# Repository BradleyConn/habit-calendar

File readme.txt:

This project contains everything used to construct a Habit Calender inspired from Simone Geirtz https://yetch.store/products/every-day-goal-calendar

This project contains the PCB designs designed in kicad as well as BOM and position files that wer sent off to JLCPCB for manufacturing.

Each board cost around $4 to make and ship and contains two PY32F002A microcontrollers and 32 lights/buttons. It takes 16 boards to make a full 365 day calendar.

The lights are ws2812b which provide endless lighting possibilities to be used outside of a calender concept. The LEDs can be controlled from the microcontroller with a bitbanged driver. A neat accomplishment from a super cheap 8 MHz microcontroller.

This wasn't intended to be public facing yet so the code is somewhat messy from when I was just trying to protoype stuff out, and documentation is not the best. In the software folder, the standalone folder is what you want, but check the readme for helpful info. Hopefully I can find some time to clean everything up.

More information and pictures can be found on www.bradleyconn.space
I need to properly cross link everything still. Sorry about that.

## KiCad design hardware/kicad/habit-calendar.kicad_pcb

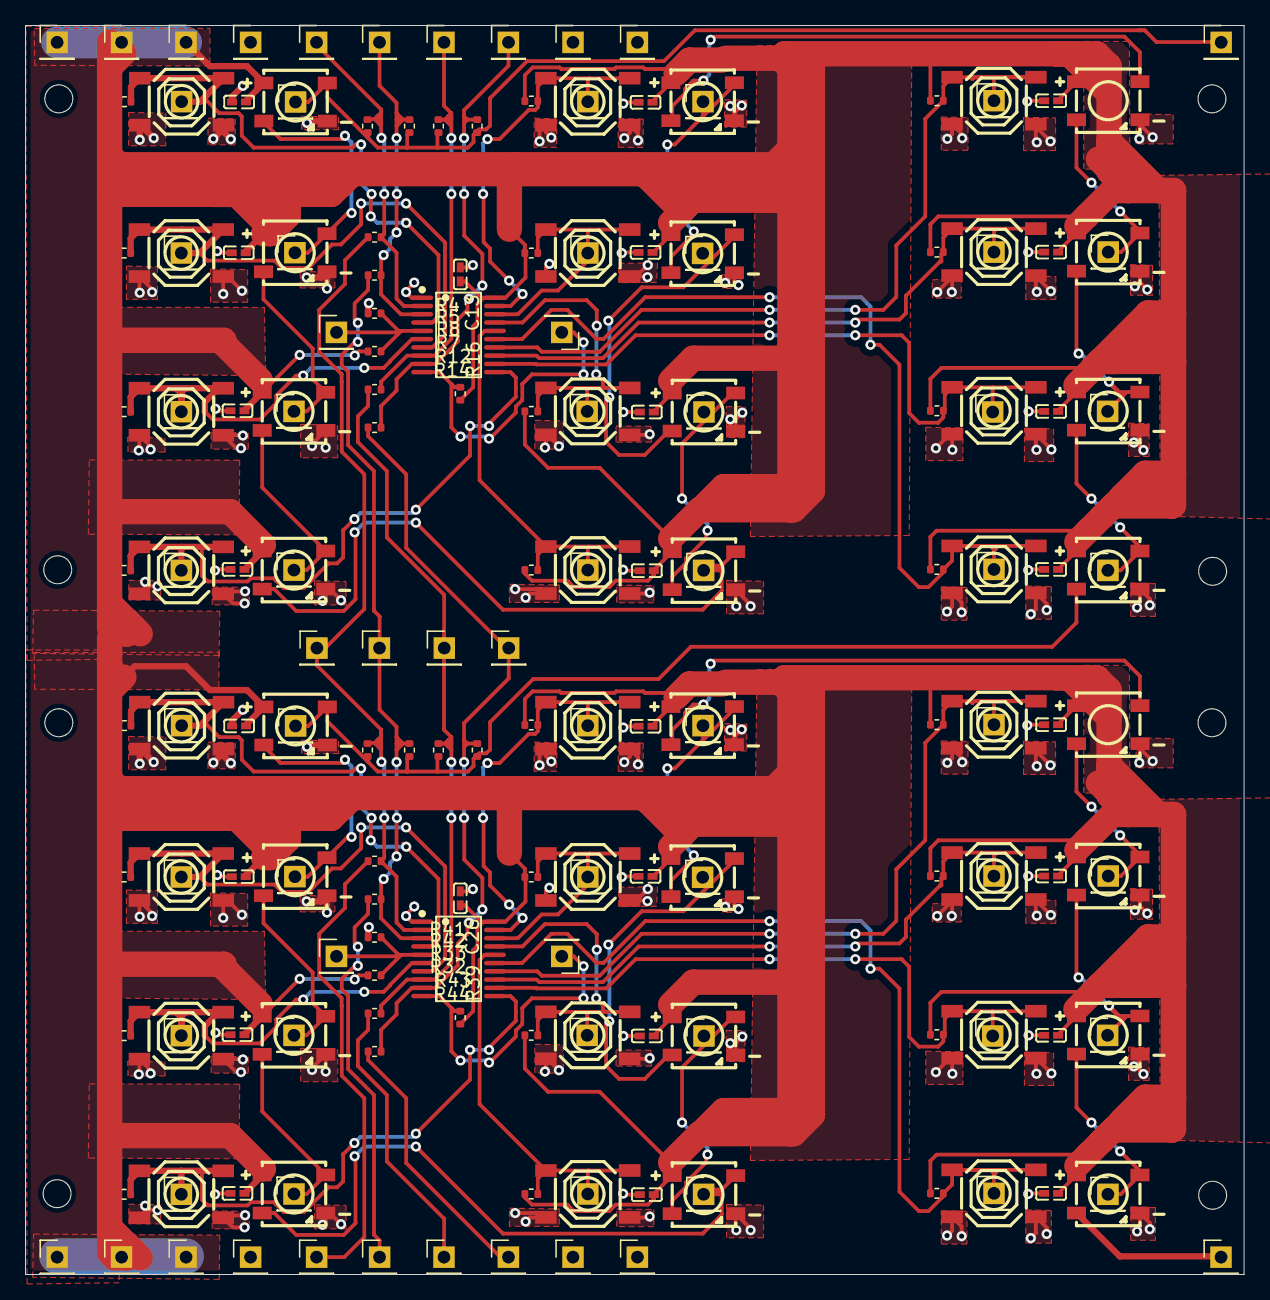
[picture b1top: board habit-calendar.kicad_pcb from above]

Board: 2 copper layers, 96.0 x 98.4 mm, 206 parts (0 on the bottom side), 67 nets.

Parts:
C1, C2, C3, C4, C5, C6, C7, C8, C9, C10, C11, C12, C13, C14, C15, C16, C17, C18, C19, C20, C21, C22, C23, C24, C25, C26: 100nf; C0402
H1, H2, H3, H4, H5, H6, H7, H8: MountingHole; MountingHole_2.2mm_M2
J1, J2, J4, J5, J6, J7, J8, J9, J10, J11, J12, J13, J14, J15, J16, J17, J18, J19, J20, J21, J22, J24, J25, J26, J27, J29, J30, J31, J32, J33, J34, J35, J36, J37, J38, J40, J41, J43, J44, J45, J46, J47, J49, J50, J51, J52, J53, J54, J55, J56, J57, J58, J59, J60, J61, J62, J63, J64, J65, J66, J67, J68, J75, J76, J77, J78, J89, J90, J91, J92, J93, J94, J95, J96, J97, J98: Conn_01x01; PinHeader_1x01_P2.54mm_Vertical
LED1, LED2, LED3, LED4, LED5, LED6, LED7, LED8, LED9, LED10, LED11, LED12, LED13, LED14, LED15, LED16, LED17, LED18, LED19, LED20, LED21, LED22, LED23, LED24: XL-5050RGBC-WS2812B; LED-SMD_4P-L5.0-W5.0-BL_XL-5050RGBC
R1, R2, R3, R6, R8, R9, R10, R11, R13, R15, R16, R17, R18, R19, R24, R25, R28, R31, R33, R34, R35, R36, R37, R38, R39, R40, R45, R46: 10k; R_0402_1005Metric
R4, R5, R12, R14, R20, R21, R22, R23, R26, R27, R29, R30, R41, R42, R43, R44: 0 ohm; R_0402_1005Metric
R7, R32: DNP; R_0402_1005Metric
SW1, SW2, SW3, SW4, SW5, SW6, SW7, SW8, SW9, SW10, SW11, SW12, SW13, SW14, SW15, SW16, SW17, SW18, SW19, SW20, SW21, SW22, SW23, SW24: TS-1187A-B-A-B; SW-SMD_4P-L5.1-W5.1-P3.70-LS6.5-TL-2
U1, U2: PY32F002AF15P6TU; TSSOP-20_L6.5-W4.4-P0.65-LS6.4-BL

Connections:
+5V: C1.2, C2.2, C3.2, C4.2, C5.2, C6.2, C7.2, C8.2, C9.2, C10.2, C11.2, C12.2, C13.2, C14.2, C15.2, C16.2, C17.2, C18.2, C19.2, C20.2, C21.2, C22.2, C23.2, C24.2, C25.2, C26.2, J4.1, J5.1, J51.1, J89.1, J90.1, J91.1, LED1.1 (VDD), LED2.1 (VDD), LED3.1 (VDD), LED4.1 (VDD), LED5.1 (VDD), LED6.1 (VDD), LED7.1 (VDD), LED8.1 (VDD), LED9.1 (VDD), LED10.1 (VDD), LED11.1 (VDD), LED12.1 (VDD), LED13.1 (VDD), LED14.1 (VDD), LED15.1 (VDD), LED16.1 (VDD), LED17.1 (VDD), LED18.1 (VDD), LED19.1 (VDD), LED20.1 (VDD), LED21.1 (VDD), LED22.1 (VDD), LED23.1 (VDD), LED24.1 (VDD), R1.2, R2.2, R3.2, R6.2, R7.1, R9.2, R10.2, R11.2, R13.2, R15.2, R16.2, R17.2, R18.2, R19.2, R24.2, R25.2, R28.2, R31.2, R32.1, R34.2, R35.2, R36.2, R37.2, R38.2, R39.2, R40.2, R45.2, R46.2, U1.20 (VCC), U2.20 (VCC)
/habit-calender-subsheet-for-replica1/PA13: J75.1, R4.1, R26.2, R41.2, U2.2 (PA13-SWD)
/habit-calender-subsheet-for-replica1/PA14: J76.1, R5.1, R27.2, R42.2, U2.3 (PA14-SWC)
/habit-calender-subsheet-for-replica1/PF0: J77.1, R12.1, R29.2, R43.2, U2.8 (PF0-OSCIN)
/habit-calender-subsheet-for-replica1/PF1: J78.1, R14.1, R30.2, R44.2, U2.9 (PF1-OSCOUT)
/habit-calender-subsheet-for-replica1/SW6: J53.1, R35.1, SW18.1 (A), SW18.2 (B), U2.7 (PA5)
/habit-calender-subsheet-for-replica1/SW8: J55.1, R37.1, SW20.1 (A), SW20.2 (B), U2.11 (PA0)
/habit-calender-subsheet-for-replica1/SW9: J58.1, R38.1, SW21.1 (A), SW21.2 (B), U2.14 (PA3)
/habit-calender-subsheet-for-replica1/SW12: J62.1, R46.1, SW24.1 (A), SW24.2 (B), U2.15 (PA4)
/habit-calender-subsheet-for-replica1/WS2812b - Din: J32.1, LED12.2 (DOU), LED13.4 (DIN), R26.1, R27.1, R29.1, R30.1
/habit-calender-subsheet-for-replica1/outLed: J46.1, LED24.2 (DOU)
/habit-calender-subsheet-for-replica1/outPA13: J95.1, R41.1
/habit-calender-subsheet-for-replica1/outPA14: J96.1, R42.1
/habit-calender-subsheet-for-replica1/outPF0: J97.1, R43.1
/habit-calender-subsheet-for-replica1/outPF1: J98.1, R44.1
/habit-calender-subsheet-for-replica/PA13: J65.1, R4.2, R20.2, U1.2 (PA13-SWD)
/habit-calender-subsheet-for-replica/PA14: J66.1, R5.2, R21.2, U1.3 (PA14-SWC)
/habit-calender-subsheet-for-replica/PF0: J67.1, R12.2, R22.2, U1.8 (PF0-OSCIN)
/habit-calender-subsheet-for-replica/PF1: J68.1, R14.2, R23.2, U1.9 (PF1-OSCOUT)
/habit-calender-subsheet-for-replica/SW6: J9.1, R10.1, SW6.1 (A), SW6.2 (B), U1.7 (PA5)
/habit-calender-subsheet-for-replica/SW8: J12.1, R13.1, SW8.1 (A), SW8.2 (B), U1.11 (PA0)
/habit-calender-subsheet-for-replica/SW9: J16.1, R15.1, SW9.1 (A), SW9.2 (B), U1.14 (PA3)
/habit-calender-subsheet-for-replica/SW12: J20.1, R19.1, SW12.1 (A), SW12.2 (B), U1.15 (PA4)
/habit-calender-subsheet-for-replica/WS2812b - Din: J11.1, J22.1, LED1.4 (DIN), R20.1, R21.1, R22.1, R23.1
GND: C1.1, C2.1, C3.1, C4.1, C5.1, C6.1, C7.1, C8.1, C9.1, C10.1, C11.1, C12.1, C13.1, C14.1, C15.1, C16.1, C17.1, C18.1, C19.1, C20.1, C21.1, C22.1, C23.1, C24.1, C25.1, C26.1, J60.1, J63.1, J64.1, J92.1, J93.1, J94.1, LED1.3 (GND), LED2.3 (GND), LED3.3 (GND), LED4.3 (GND), LED5.3 (GND), LED6.3 (GND), LED7.3 (GND), LED8.3 (GND), LED9.3 (GND), LED10.3 (GND), LED11.3 (GND), LED12.3 (GND), LED13.3 (GND), LED14.3 (GND), LED15.3 (GND), LED16.3 (GND), LED17.3 (GND), LED18.3 (GND), LED19.3 (GND), LED20.3 (GND), LED21.3 (GND), LED22.3 (GND), LED23.3 (GND), LED24.3 (GND), R8.1, R33.1, SW1.3 (C), SW1.4 (D), SW2.3 (C), SW2.4 (D), SW3.3 (C), SW3.4 (D), SW4.3 (C), SW4.4 (D), SW5.3 (C), SW5.4 (D), SW6.3 (C), SW6.4 (D), SW7.3 (C), SW7.4 (D), SW8.3 (C), SW8.4 (D), SW9.3 (C), SW9.4 (D), SW10.3 (C), SW10.4 (D), SW11.3 (C), SW11.4 (D), SW12.3 (C), SW12.4 (D), SW13.3 (C), SW13.4 (D), SW14.3 (C), SW14.4 (D), SW15.3 (C), SW15.4 (D), SW16.3 (C), SW16.4 (D), SW17.3 (C), SW17.4 (D), SW18.3 (C), SW18.4 (D), SW19.3 (C), SW19.4 (D), SW20.3 (C), SW20.4 (D), SW21.3 (C), SW21.4 (D), SW22.3 (C), SW22.4 (D), SW23.3 (C), SW23.4 (D), SW24.3 (C), SW24.4 (D), U1.1 (VSS), U2.1 (VSS)
unnamed: J1.1, R1.1, SW1.1 (A), SW1.2 (B), U1.19 (PB1)
unnamed: J2.1, R2.1, SW2.1 (A), SW2.2 (B), U1.18 (PB2)
unnamed: J6.1, R3.1, SW3.1 (A), SW3.2 (B), U1.17 (PB0)
unnamed: J7.1, R6.1, SW4.1 (A), SW4.2 (B), U1.16 (PA7)
unnamed: J8.1, R7.2, R8.2, U1.5 (PB6/PF4-BOOT0)
unnamed: J10.1, R9.1, SW5.1 (A), SW5.2 (B), U1.4 (PB3)
unnamed: J13.1, R11.1, SW7.1 (A), SW7.2 (B), U1.6 (PA6)
unnamed: J14.1, LED1.2 (DOU), LED2.4 (DIN)
unnamed: J15.1, R16.1, U1.10 (PF2-NRST)
unnamed: J17.1, R17.1, SW10.1 (A), SW10.2 (B), U1.13 (PA2)
unnamed: J18.1, R18.1, SW11.1 (A), SW11.2 (B), U1.12 (PA1)
unnamed: J19.1, LED2.2 (DOU), LED3.4 (DIN)
unnamed: J21.1, LED3.2 (DOU), LED4.4 (DIN)
unnamed: J24.1, LED5.4 (DIN), LED6.2 (DOU)
unnamed: J25.1, LED6.4 (DIN), LED7.2 (DOU)
unnamed: J26.1, LED7.4 (DIN), LED8.2 (DOU)
unnamed: J27.1, LED4.2 (DOU), LED8.4 (DIN)
unnamed: LED5.2 (DOU), LED9.4 (DIN)
unnamed: J29.1, LED9.2 (DOU), LED10.4 (DIN)
unnamed: J30.1, LED10.2 (DOU), LED11.4 (DIN)
unnamed: J31.1, LED11.2 (DOU), LED12.4 (DIN)
unnamed: J33.1, LED13.2 (DOU), LED14.4 (DIN)
unnamed: J34.1, LED14.2 (DOU), LED15.4 (DIN)
unnamed: J35.1, LED15.2 (DOU), LED16.4 (DIN)
unnamed: J36.1, LED17.4 (DIN), LED18.2 (DOU)
unnamed: J37.1, LED18.4 (DIN), LED19.2 (DOU)
unnamed: J38.1, LED19.4 (DIN), LED20.2 (DOU)
unnamed: J40.1, R24.1, SW13.1 (A), SW13.2 (B), U2.19 (PB1)
unnamed: J41.1, LED16.2 (DOU), LED20.4 (DIN)
unnamed: LED17.2 (DOU), LED21.4 (DIN)
unnamed: J43.1, LED21.2 (DOU), LED22.4 (DIN)
unnamed: J44.1, LED22.2 (DOU), LED23.4 (DIN)
unnamed: J45.1, LED23.2 (DOU), LED24.4 (DIN)
unnamed: J47.1, R25.1, SW14.1 (A), SW14.2 (B), U2.18 (PB2)
unnamed: J49.1, R28.1, SW15.1 (A), SW15.2 (B), U2.17 (PB0)
unnamed: J50.1, R31.1, SW16.1 (A), SW16.2 (B), U2.16 (PA7)
unnamed: J52.1, R32.2, R33.2, U2.5 (PB6/PF4-BOOT0)
unnamed: J54.1, R34.1, SW17.1 (A), SW17.2 (B), U2.4 (PB3)
unnamed: J56.1, R36.1, SW19.1 (A), SW19.2 (B), U2.6 (PA6)
unnamed: J57.1, R39.1, U2.10 (PF2-NRST)
unnamed: J59.1, R40.1, SW22.1 (A), SW22.2 (B), U2.13 (PA2)
unnamed: J61.1, R45.1, SW23.1 (A), SW23.2 (B), U2.12 (PA1)

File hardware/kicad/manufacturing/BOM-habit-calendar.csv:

Comment,Designator,Footprint,LCSC
100nf,"C1,C10,C11,C12,C14,C15,C16,C17,C18,C19,C2,C20,C21,C22,C23,C24,C25,C3,C4,C5,C6,C7,C8,C9",C0402,C1525
XL-5050RGBC-WS2812B,"LED1,LED10,LED11,LED12,LED13,LED14,LED15,LED16,LED17,LED18,LED19,LED2,LED20,LED21,LED22,LED23,LED24,LED3,LED4,LED5,LED6,LED7,LED8,LED9",LED-SMD_4P-L5.0-W5.0-BL_XL-5050RGBC,C2843785
TS-1187A-B-A-B,"SW1,SW10,SW11,SW12,SW13,SW14,SW15,SW16,SW17,SW18,SW19,SW2,SW20,SW21,SW22,SW23,SW24,SW3,SW4,SW5,SW6,SW7,SW8,SW9",SW-SMD_4P-L5.1-W5.1-P3.70-LS6.5-TL-2,C318884
PY32F002AF15P6TU,"U1,U2",TSSOP-20_L6.5-W4.4-P0.65-LS6.4-BL,C5292059
Conn_01x01,J78,PinHeader_1x01_P2.54mm_Vertical,
Conn_01x01,J77,PinHeader_1x01_P2.54mm_Vertical,
Conn_01x01,J76,PinHeader_1x01_P2.54mm_Vertical,
Conn_01x01,J75,PinHeader_1x01_P2.54mm_Vertical,
10k,R46,R_0402_1005Metric,
10k,R45,R_0402_1005Metric,
0 ohm,R44,R_0402_1005Metric,
0 ohm,R43,R_0402_1005Metric,
0 ohm,R42,R_0402_1005Metric,
0 ohm,R41,R_0402_1005Metric,
10k,R40,R_0402_1005Metric,
10k,R39,R_0402_1005Metric,
10k,R38,R_0402_1005Metric,
10k,R37,R_0402_1005Metric,
10k,R36,R_0402_1005Metric,
10k,R35,R_0402_1005Metric,
10k,R34,R_0402_1005Metric,
10k,R33,R_0402_1005Metric,
DNP,R32,R_0402_1005Metric,
10k,R31,R_0402_1005Metric,
0 ohm,R30,R_0402_1005Metric,
0 ohm,R29,R_0402_1005Metric,
10k,R28,R_0402_1005Metric,
0 ohm,R27,R_0402_1005Metric,
0 ohm,R26,R_0402_1005Metric,
10k,R25,R_0402_1005Metric,
10k,R24,R_0402_1005Metric,
Conn_01x01,J98,PinHeader_1x01_P2.54mm_Vertical,
Conn_01x01,J97,PinHeader_1x01_P2.54mm_Vertical,
Conn_01x01,J96,PinHeader_1x01_P2.54mm_Vertical,
Conn_01x01,J95,PinHeader_1x01_P2.54mm_Vertical,
Conn_01x01,J94,PinHeader_1x01_P2.54mm_Vertical,
Conn_01x01,J93,PinHeader_1x01_P2.54mm_Vertical,
Conn_01x01,J92,PinHeader_1x01_P2.54mm_Vertical,
Conn_01x01,J91,PinHeader_1x01_P2.54mm_Vertical,
Conn_01x01,J90,PinHeader_1x01_P2.54mm_Vertical,
Conn_01x01,J89,PinHeader_1x01_P2.54mm_Vertical,
Conn_01x01,J62,PinHeader_1x01_P2.54mm_Vertical,
Conn_01x01,J61,PinHeader_1x01_P2.54mm_Vertical,
Conn_01x01,J59,PinHeader_1x01_P2.54mm_Vertical,
Conn_01x01,J58,PinHeader_1x01_P2.54mm_Vertical,
Conn_01x01,J57,PinHeader_1x01_P2.54mm_Vertical,
Conn_01x01,J56,PinHeader_1x01_P2.54mm_Vertical,
Conn_01x01,J55,PinHeader_1x01_P2.54mm_Vertical,
Conn_01x01,J54,PinHeader_1x01_P2.54mm_Vertical,
Conn_01x01,J53,PinHeader_1x01_P2.54mm_Vertical,
Conn_01x01,J52,PinHeader_1x01_P2.54mm_Vertical,
Conn_01x01,J50,PinHeader_1x01_P2.54mm_Vertical,
Conn_01x01,J49,PinHeader_1x01_P2.54mm_Vertical,
Conn_01x01,J47,PinHeader_1x01_P2.54mm_Vertical,
Conn_01x01,J46,PinHeader_1x01_P2.54mm_Vertical,
Conn_01x01,J45,PinHeader_1x01_P2.54mm_Vertical,
Conn_01x01,J44,PinHeader_1x01_P2.54mm_Vertical,
Conn_01x01,J43,PinHeader_1x01_P2.54mm_Vertical,
Conn_01x01,J41,PinHeader_1x01_P2.54mm_Vertical,
Conn_01x01,J40,PinHeader_1x01_P2.54mm_Vertical,
Conn_01x01,J38,PinHeader_1x01_P2.54mm_Vertical,
Conn_01x01,J37,PinHeader_1x01_P2.54mm_Vertical,
Conn_01x01,J36,PinHeader_1x01_P2.54mm_Vertical,
Conn_01x01,J35,PinHeader_1x01_P2.54mm_Vertical,
Conn_01x01,J34,PinHeader_1x01_P2.54mm_Vertical,
Conn_01x01,J33,PinHeader_1x01_P2.54mm_Vertical,
Conn_01x01,J32,PinHeader_1x01_P2.54mm_Vertical,
MountingHole,H8,MountingHole_2.2mm_M2,
MountingHole,H7,MountingHole_2.2mm_M2,
MountingHole,H6,MountingHole_2.2mm_M2,
MountingHole,H5,MountingHole_2.2mm_M2,
100nf,C26,C0402,
Conn_01x01,J10,PinHeader_1x01_P2.54mm_Vertical,
10k,R19,R_0402_1005Metric,
Conn_01x01,J63,PinHeader_1x01_P2.54mm_Vertical,
Conn_01x01,J67,PinHeader_1x01_P2.54mm_Vertical,
Conn_01x01,J21,PinHeader_1x01_P2.54mm_Vertical,
Conn_01x01,J5,PinHeader_1x01_P2.54mm_Vertical,
Conn_01x01,J15,PinHeader_1x01_P2.54mm_Vertical,
10k,R9,R_0402_1005Metric,
0 ohm,R22,R_0402_1005Metric,
Conn_01x01,J9,PinHeader_1x01_P2.54mm_Vertical,
10k,R13,R_0402_1005Metric,
0 ohm,R14,R_0402_1005Metric,
Conn_01x01,J2,PinHeader_1x01_P2.54mm_Vertical,
Conn_01x01,J20,PinHeader_1x01_P2.54mm_Vertical,
Conn_01x01,J30,PinHeader_1x01_P2.54mm_Vertical,
Conn_01x01,J22,PinHeader_1x01_P2.54mm_Vertical,
Conn_01x01,J13,PinHeader_1x01_P2.54mm_Vertical,
10k,R8,R_0402_1005Metric,
Conn_01x01,J31,PinHeader_1x01_P2.54mm_Vertical,
Conn_01x01,J11,PinHeader_1x01_P2.54mm_Vertical,
MountingHole,H1,MountingHole_2.2mm_M2,
Conn_01x01,J1,PinHeader_1x01_P2.54mm_Vertical,
Conn_01x01,J66,PinHeader_1x01_P2.54mm_Vertical,
MountingHole,H2,MountingHole_2.2mm_M2,
MountingHole,H3,MountingHole_2.2mm_M2,
0 ohm,R20,R_0402_1005Metric,
Conn_01x01,J29,PinHeader_1x01_P2.54mm_Vertical,
10k,R2,R_0402_1005Metric,
10k,R10,R_0402_1005Metric,
10k,R18,R_0402_1005Metric,
10k,R11,R_0402_1005Metric,
Conn_01x01,J4,PinHeader_1x01_P2.54mm_Vertical,
100nf,C13,C0402,
Conn_01x01,J65,PinHeader_1x01_P2.54mm_Vertical,
DNP,R7,R_0402_1005Metric,
Conn_01x01,J18,PinHeader_1x01_P2.54mm_Vertical,
MountingHole,H4,MountingHole_2.2mm_M2,
0 ohm,R12,R_0402_1005Metric,
Conn_01x01,J27,PinHeader_1x01_P2.54mm_Vertical,
10k,R17,R_0402_1005Metric,
10k,R1,R_0402_1005Metric,
Conn_01x01,J6,PinHeader_1x01_P2.54mm_Vertical,
0 ohm,R23,R_0402_1005Metric,
Conn_01x01,J25,PinHeader_1x01_P2.54mm_Vertical,
0 ohm,R4,R_0402_1005Metric,
Conn_01x01,J26,PinHeader_1x01_P2.54mm_Vertical,
Conn_01x01,J16,PinHeader_1x01_P2.54mm_Vertical,
10k,R16,R_0402_1005Metric,
Conn_01x01,J64,PinHeader_1x01_P2.54mm_Vertical,
10k,R6,R_0402_1005Metric,
Conn_01x01,J51,PinHeader_1x01_P2.54mm_Vertical,
Conn_01x01,J12,PinHeader_1x01_P2.54mm_Vertical,
Conn_01x01,J68,PinHeader_1x01_P2.54mm_Vertical,
Conn_01x01,J24,PinHeader_1x01_P2.54mm_Vertical,
0 ohm,R21,R_0402_1005Metric,
10k,R15,R_0402_1005Metric,
Conn_01x01,J60,PinHeader_1x01_P2.54mm_Vertical,
Conn_01x01,J17,PinHeader_1x01_P2.54mm_Vertical,
Conn_01x01,J8,PinHeader_1x01_P2.54mm_Vertical,
0 ohm,R5,R_0402_1005Metric,
10k,R3,R_0402_1005Metric,
Conn_01x01,J7,PinHeader_1x01_P2.54mm_Vertical,
Conn_01x01,J19,PinHeader_1x01_P2.54mm_Vertical,
Conn_01x01,J14,PinHeader_1x01_P2.54mm_Vertical,

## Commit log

2023-04-21 Initial commit. Import py32f002a part form easyeda2kicad
2023-04-22 Place components about to start routing.
2023-04-24 One micor ready. About to double the board.
2023-04-25 Got it. Just needs a logo.
2023-04-25 small tweaks but still single board. might change up edge connector
2023-04-26 Moved to a new heirarchical sheet. Instantiated two. Some PCB tweeks. Added Logo. Now going to use the replicate plugin to make another copy.
2023-04-26 Sent to production!
2023-09-13 Add code
2023-09-13 Add more to readme
2023-09-13 Add submodule
2023-09-16 Purge submodule
2023-09-17 Fix submodule stuff
2023-09-17 Add pico master to readme.
2023-09-18 Add pico_master files
2023-09-18 Update readme and code for pico-master. Untested blocking bitbang uart
2023-09-19 Working bitbanged uart at 9600 baud
2023-09-19 More accurate baudrate to fix errors.
2023-09-20 Working RX! - think you need a delay between readings...
2023-09-20 Remove all the standalone code.
2023-09-21 Two half duplex uarts!
2023-09-21 Appears to work with two half duplex's
2023-09-21 Check buttons even when waiting for rx!
2023-09-21 Remove the extra settings code.
2023-09-22 Should be all the logic working but I can't test rn. Need to change pinout based on ID still
2023-09-22 Changed based on ID - make printing bytes its own helper function
2023-11-20 Create a readme
2023-11-22 Add stacked pcb gerber pdf
